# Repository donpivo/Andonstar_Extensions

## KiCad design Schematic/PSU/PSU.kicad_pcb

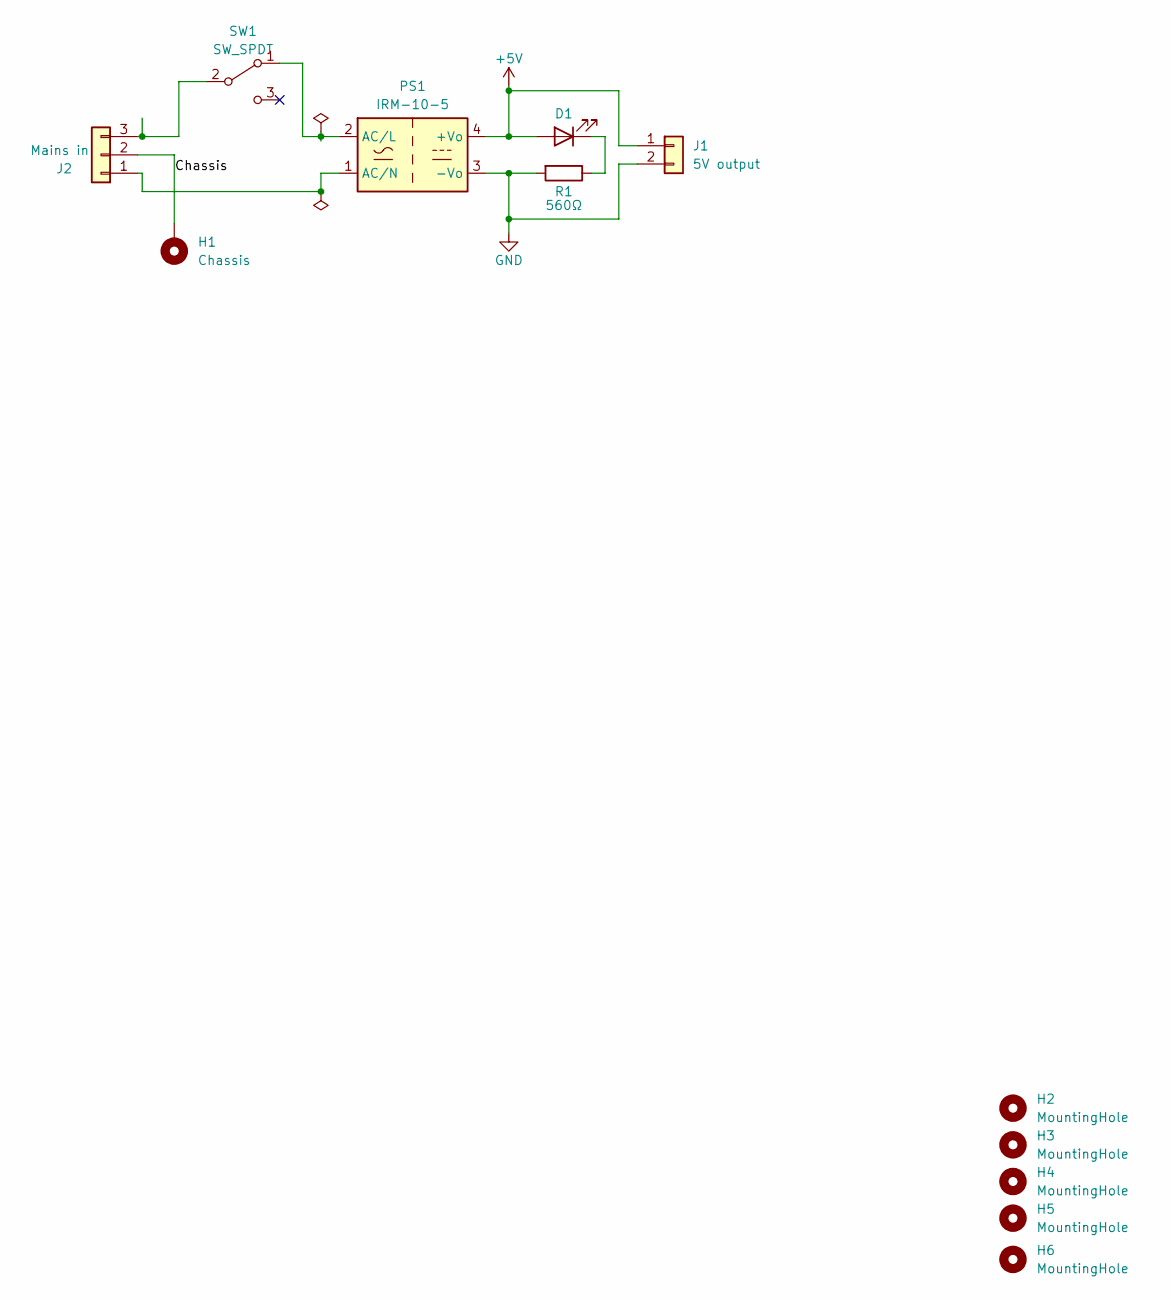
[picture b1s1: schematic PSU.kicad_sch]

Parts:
D1: Everlight 27-21/R6C-AM2N2LY/3C; LED_Everlight_Side_1x2.1mm
H1: Chassis; MountingHole_4.3mm_M4_Pad_Via
H2, H3, H4, H5, H6: MountingHole; MountingHole_3.2mm_M3
J1: 5V output; Molex_KK-254_AE-6410-02A_1x02_P2.54mm_Vertical
J2: Mains in; ScrewTerminal_DB128L-5.08-3P-BK-S
PS1: IRM-10-5; Converter_ACDC_MeanWell_IRM-10-xx_THT
R1: 560Ω; R_0805_2012Metric_Pad1.20x1.40mm_HandSolder
SW1: SW_SPDT; 1101M2S3ABE2

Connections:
+5V: D1.2 (A), J1.1, PS1.4 (+Vo)
/Chassis: H1.1, J2.2
GND: J1.2, PS1.3 (-Vo), R1.2
unnamed: D1.1 (K), R1.1
unnamed: J2.1, PS1.1 (AC/N)
unnamed: J2.3, SW1.2 (B)
unnamed: PS1.2 (AC/L), SW1.1 (A)

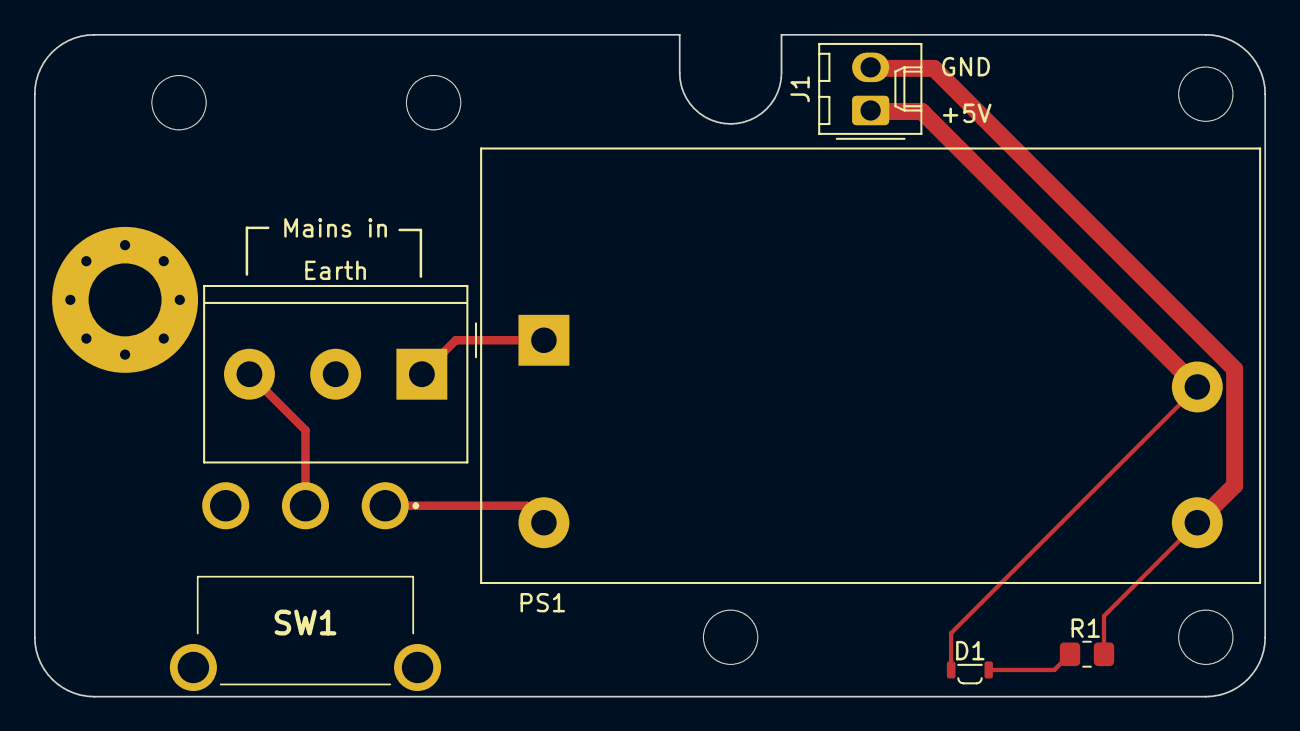
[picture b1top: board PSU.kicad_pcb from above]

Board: 2 copper layers, 72.5 x 39.0 mm, 12 parts (0 on the bottom side), 7 nets.

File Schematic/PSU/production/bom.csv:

Designator,Footprint,Quantity,Value,LCSC Part #
D1,LED_Everlight_Side_1x2.1mm,1,LED,
H1,MountingHole_4.3mm_M4_Pad_Via,1,Chassis,
"H2, H3, H4, H5, H6",MountingHole_3.2mm_M3,5,MountingHole,
J1,Molex_KK-254_AE-6410-02A_1x02_P2.54mm_Vertical,1,5V output,
J2,ScrewTerminal_DB128L-5.08-3P-BK-S,1,Mains in,
PS1,Converter_ACDC_MeanWell_IRM-10-xx_THT,1,IRM-10-5,
R1,0805,1,560Ω,
SW1,1101M2S3ABE2,1,SW_SPDT,

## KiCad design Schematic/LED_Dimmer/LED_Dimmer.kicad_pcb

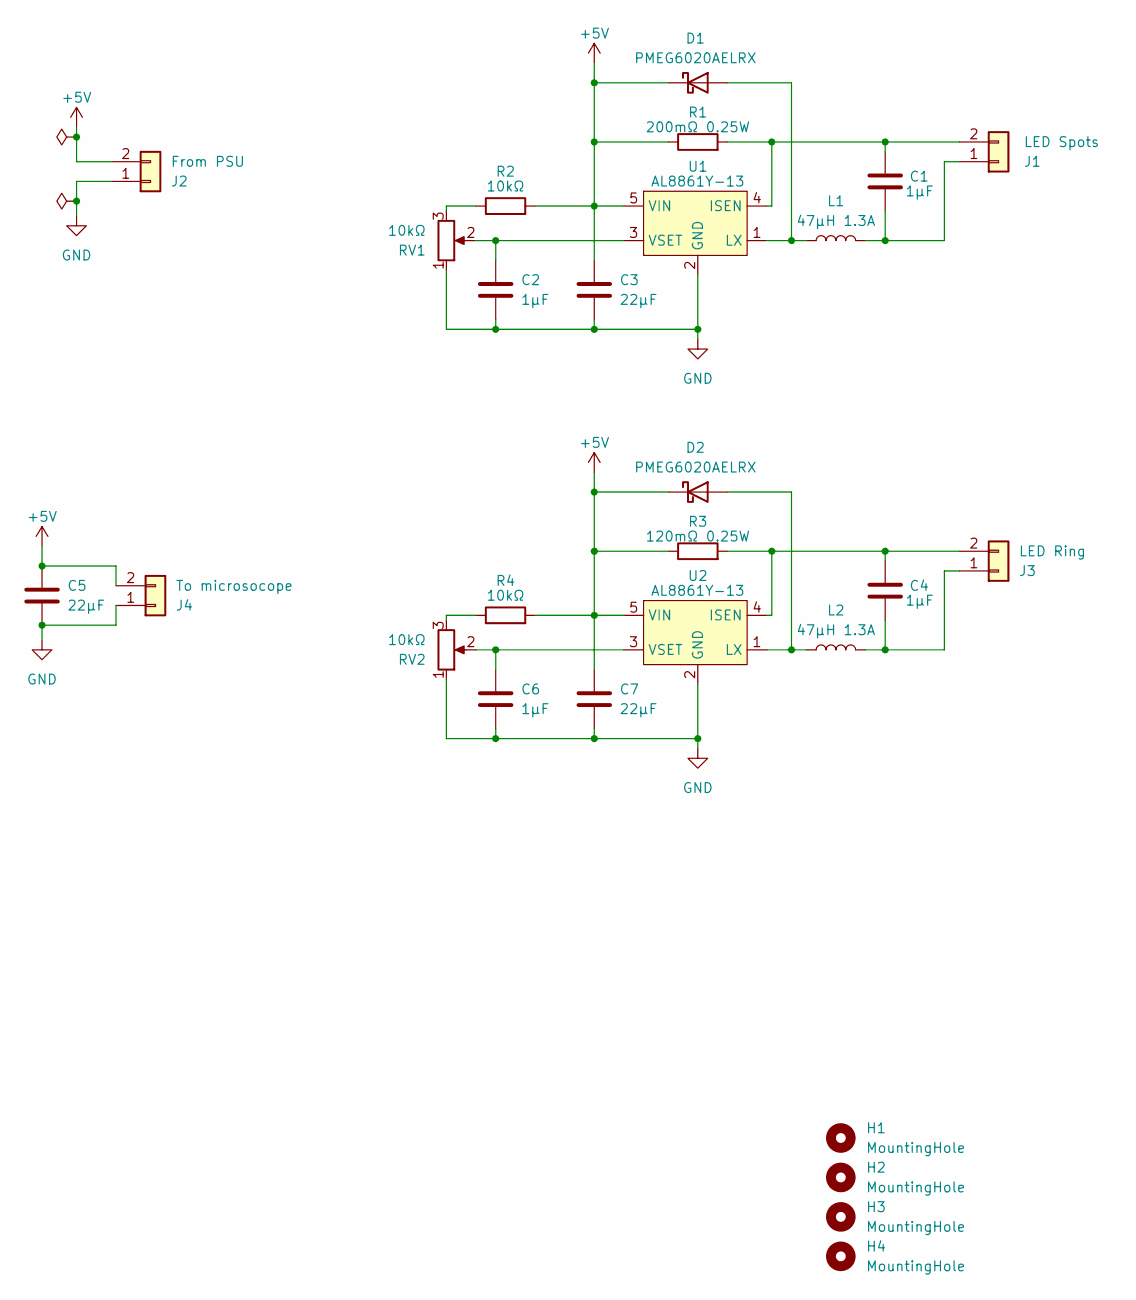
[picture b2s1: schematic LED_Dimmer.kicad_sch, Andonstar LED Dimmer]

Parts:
C1, C2, C4, C6: 1µF; R_0805_2012Metric_Pad1.20x1.40mm_HandSolder
C3, C5, C7: 22µF; R_0805_2012Metric_Pad1.20x1.40mm_HandSolder
D1, D2: PMEG6020AELRX; Nexperia_CFP3_SOD-123W
H1, H2, H3: MountingHole; MountingHole_3.2mm_M3
H4: MountingHole; MountingHole_4.3mm_M4
J1: LED Spots; KF2510-2P-Angle
J2: From PSU; KF2510-2P-Angle
J3: LED Ring; KF2510-2P-Angle
J4: To microsocope; KF2510-2P-Angle
L1, L2: 47µH 1.3A; VLS6045
R1: 200mΩ 0.25W; R_1206_3216Metric_Pad1.30x1.75mm_HandSolder
R2, R4: 10kΩ; R_0805_2012Metric_Pad1.20x1.40mm_HandSolder
R3: 120mΩ 0.25W; R_1206_3216Metric_Pad1.30x1.75mm_HandSolder
RV1, RV2: 10kΩ; Potentiometer_Alps_RK09K_Single_Vertical
U1, U2: AL8861Y-13; SOT89-5

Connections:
+5V: C3.1, C5.1, C7.1, D1.1 (K), D2.1 (K), J2.2, J4.2, R1.1, R2.2, R3.1, R4.2, U1.5 (VIN), U2.5 (VIN)
GND: C2.2, C3.2, C5.2, C6.2, C7.2, J2.1, J4.1, RV1.1, RV2.1, U1.2 (GND), U2.2 (GND)
unnamed: D1.2 (A), L1.1, U1.1 (LX)
unnamed: D2.2 (A), L2.1, U2.1 (LX)
unnamed: C1.1, J1.1, L1.2
unnamed: C1.2, J1.2, R1.2, U1.4 (ISEN)
unnamed: C4.1, J3.1, L2.2
unnamed: C4.2, J3.2, R3.2, U2.4 (ISEN)
unnamed: R2.1, RV1.3
unnamed: R4.1, RV2.3
unnamed: C2.1, RV1.2, U1.3 (VSET)
unnamed: C6.1, RV2.2, U2.3 (VSET)

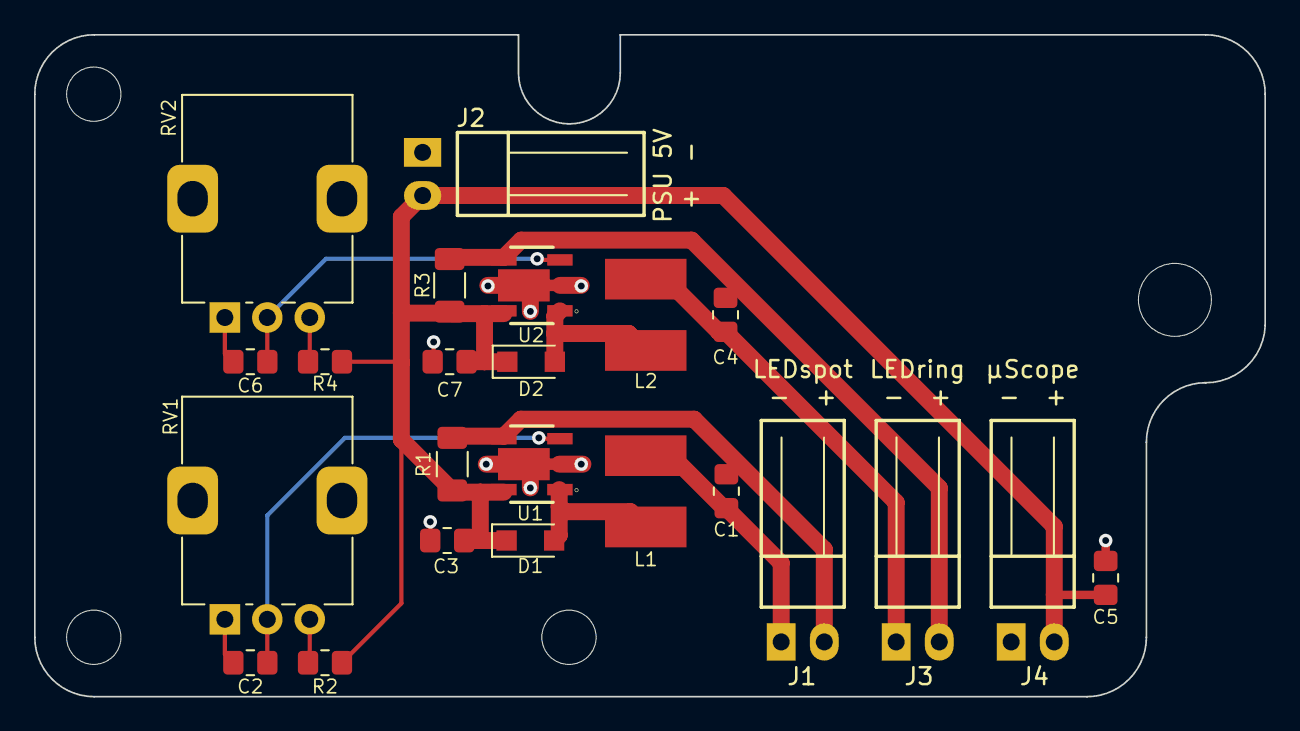
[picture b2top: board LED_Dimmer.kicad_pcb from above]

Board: 2 copper layers, 72.5 x 39.0 mm, 27 parts (0 on the bottom side), 12 nets.

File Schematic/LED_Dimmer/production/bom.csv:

Designator,Footprint,Quantity,Value,LCSC Part #
"C1, C2, C4, C6",0805,4,1µF,
"C3, C5, C7",0805,3,22µF,
"D1, D2",Nexperia_CFP3_SOD-123W,2,PMEG6020AELRX,
"H1, H2, H3",MountingHole_3.2mm_M3,3,MountingHole,
H4,MountingHole_4.3mm_M4,1,MountingHole,
J1,KF2510-2P-Angle,1,LED Spots,
J2,KF2510-2P-Angle,1,From PSU,
J3,KF2510-2P-Angle,1,LED Ring,
J4,KF2510-2P-Angle,1,To microsocope,
"L1, L2",VLS6045,2,47µH 1.3A,
R1,1206,1,200mΩ 0.25W,
"R2, R4",0805,2,10kΩ,
R3,1206,1,120mΩ 0.25W,
"RV1, RV2",Potentiometer_Alps_RK09K_Single_Vertical,2,10kΩ,
"U1, U2",SOT89-5,2,AL8861Y-13,

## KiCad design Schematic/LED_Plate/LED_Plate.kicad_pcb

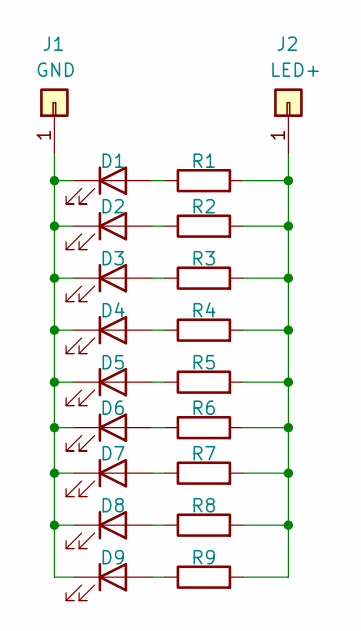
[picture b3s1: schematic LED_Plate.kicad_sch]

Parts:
D1, D2, D3, D4, D5, D6, D7, D8, D9: LED; GWJELMS1EMH2H6XX55165R33
J1: GND; TestPoint_Pad_D2.0mm
J2: LED+; TestPoint_Pad_D2.0mm
R1, R2, R3, R4, R5, R6, R7, R8, R9: 4.7Ω; R_0805_2012Metric_Pad1.20x1.40mm_HandSolder

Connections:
unnamed: D1.2 (A), R1.1
unnamed: D1.1 (K), D2.1 (K), D3.1 (K), D4.1 (K), D5.1 (K), D6.1 (K), D7.1 (K), D8.1 (K), D9.1 (K), J1.1
unnamed: D2.2 (A), R2.1
unnamed: D3.2 (A), R3.1
unnamed: D4.2 (A), R4.1
unnamed: D5.2 (A), R5.1
unnamed: D6.2 (A), R6.1
unnamed: D7.2 (A), R7.1
unnamed: D8.2 (A), R8.1
unnamed: D9.2 (A), R9.1
unnamed: J2.1, R1.2, R2.2, R3.2, R4.2, R5.2, R6.2, R7.2, R8.2, R9.2

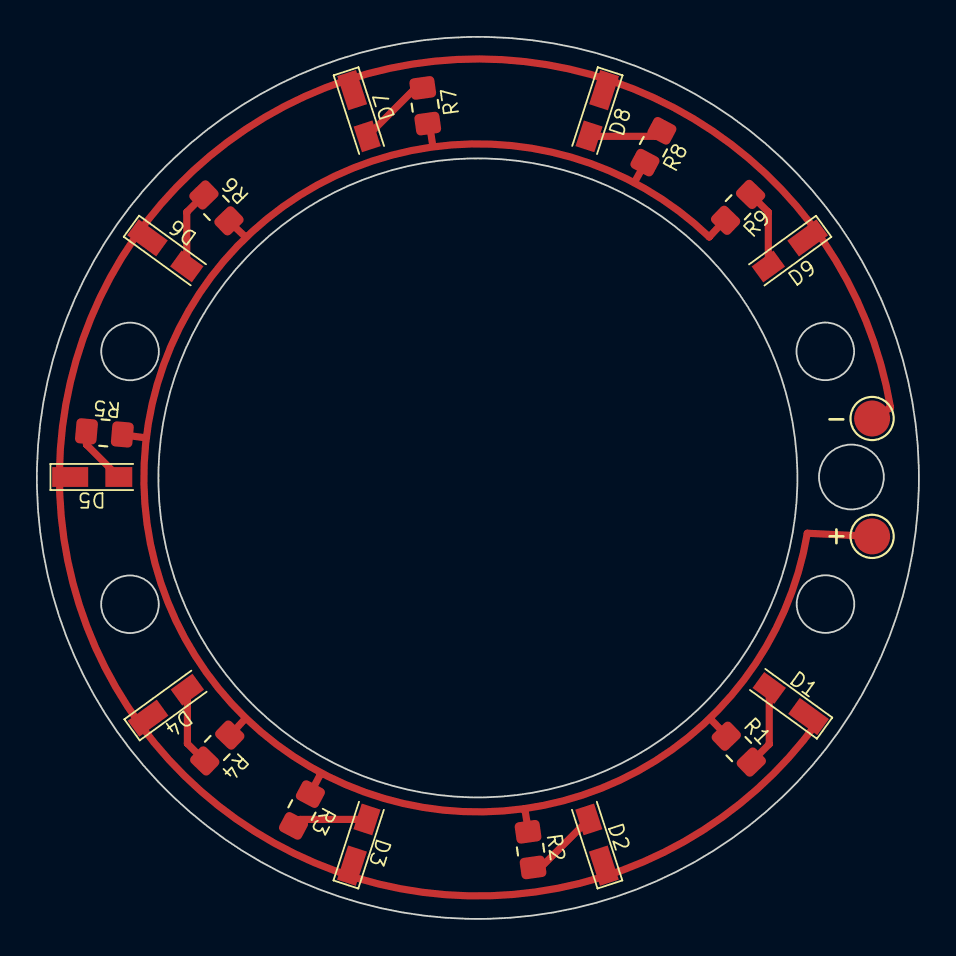
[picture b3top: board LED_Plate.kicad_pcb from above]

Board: 2 copper layers, 49.0 x 49.0 mm, 20 parts (0 on the bottom side), 11 nets.

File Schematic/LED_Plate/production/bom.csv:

Designator,Footprint,Quantity,Value,LCSC Part #
"D1, D2, D3, D4, D5, D6, D7, D8, D9",GWJELMS1EMH2H6XX55165R33,9,LED,
J1,TestPoint_Pad_D2.0mm,1,GND,
J2,TestPoint_Pad_D2.0mm,1,LED+,
"R1, R2, R3, R4, R5, R6, R7, R8, R9",0805,9,4.7Ω,

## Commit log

2023-08-05 Adjusted mounting hole position
2023-08-20 New PCB layout
2023-09-03 Updated models
2023-09-03 File cleanup
2023-09-05 Updated production files
